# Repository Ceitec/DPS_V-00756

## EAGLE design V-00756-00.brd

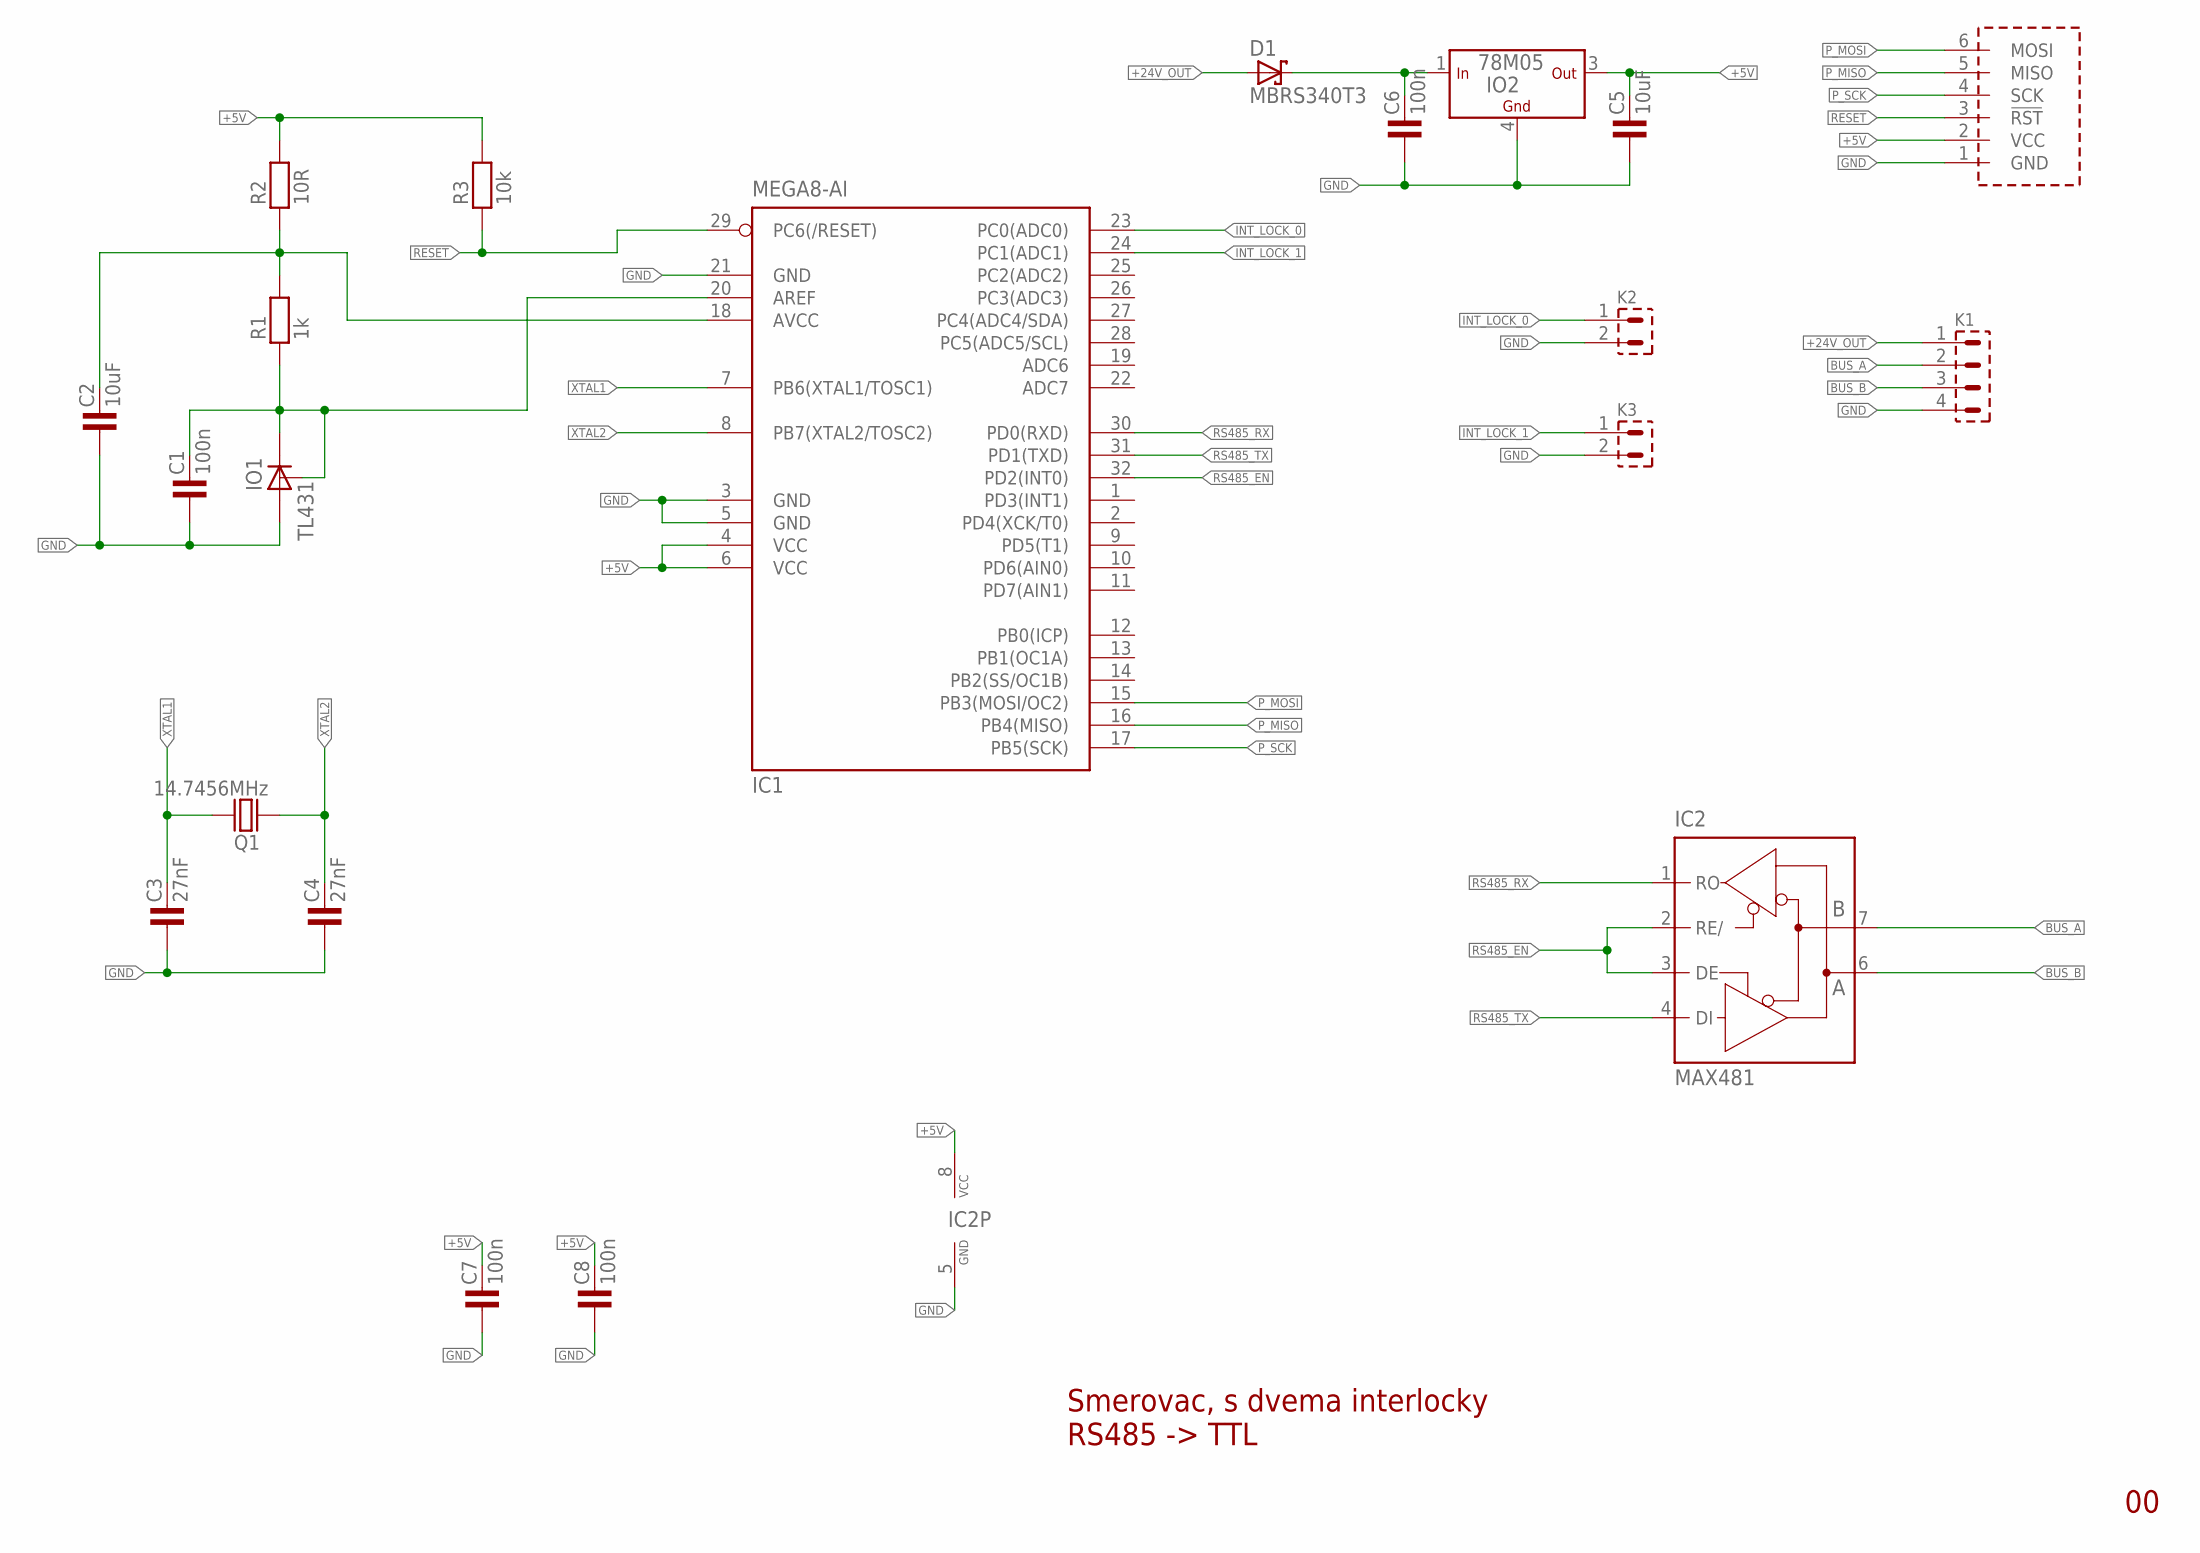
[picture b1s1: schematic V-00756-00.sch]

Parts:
C1, C6, C7, C8: 100n; 1206
C2, C5: 10uF; 1206
C3, C4: 27nF; 0805
D1: MBRS340T3; SMC
IC1: MEGA8-AI; TQFP32-08
IC2: MAX481; SO08
IO1: TL431; SOT23
IO2: 78M05; DPAK
K1: PSH02-04W
K2, K3: PSH02-02W
Q1: 14.7456MHz; HC-49U
R1: 1k; 1206
R2: 10R; 1206
R3: 10k; 1206
U$1: AVR_PROG_SPI; PSH02-06P

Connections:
+5V: C5.2, C7.2, C8.2, IC1.4 (VCC), IC1.6 (VCC), IC2.8 (VCC), IO2.3 (OUT), R2.2, R3.2, U$1.2 (VCC)
+24V: C6.2, D1.C, IO2.1 (IN)
+24V_OUT: D1.A, K1.1
AREF: C1.2, IC1.20 (AREF), IO1.1 (C), IO1.2 (R), R1.1
AVCC: C2.2, IC1.18 (AVCC), R1.2, R2.1
BUS_A: IC2.7 (B), K1.2
BUS_B: IC2.6 (A), K1.3
GND: C1.1, C2.1, C3.1, C4.1, C5.1, C6.1, C7.1, C8.1, IC1.3 (GND), IC1.5 (GND), IC1.21 (GND), IC2.5 (GND), IO1.3 (A), IO2.4 (GND), K1.4, K2.2, K3.2, U$1.1 (GND)
INT_LOCK_0: IC1.23 (PC0(ADC0)), K2.1
INT_LOCK_1: IC1.24 (PC1(ADC1)), K3.1
P_MISO: IC1.16 (PB4(MISO)), U$1.5 (MISO)
P_MOSI: IC1.15 (PB3(MOSI/OC2)), U$1.6 (MOSI)
P_SCK: IC1.17 (PB5(SCK)), U$1.4 (SCK)
RESET: IC1.29 (PC6(/RESET)), R3.1, U$1.3 (!RST)
RS485_EN: IC1.32 (PD2(INT0)), IC2.2 (RE/), IC2.3 (DE)
RS485_RX: IC1.30 (PD0(RXD)), IC2.1 (RO)
RS485_TX: IC1.31 (PD1(TXD)), IC2.4 (DI)
XTAL1: C3.2, IC1.7 (PB6(XTAL1/TOSC1)), Q1.2
XTAL2: C4.2, IC1.8 (PB7(XTAL2/TOSC2)), Q1.1

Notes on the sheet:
Smerovac, s dvema interlocky RS485 -> TTL

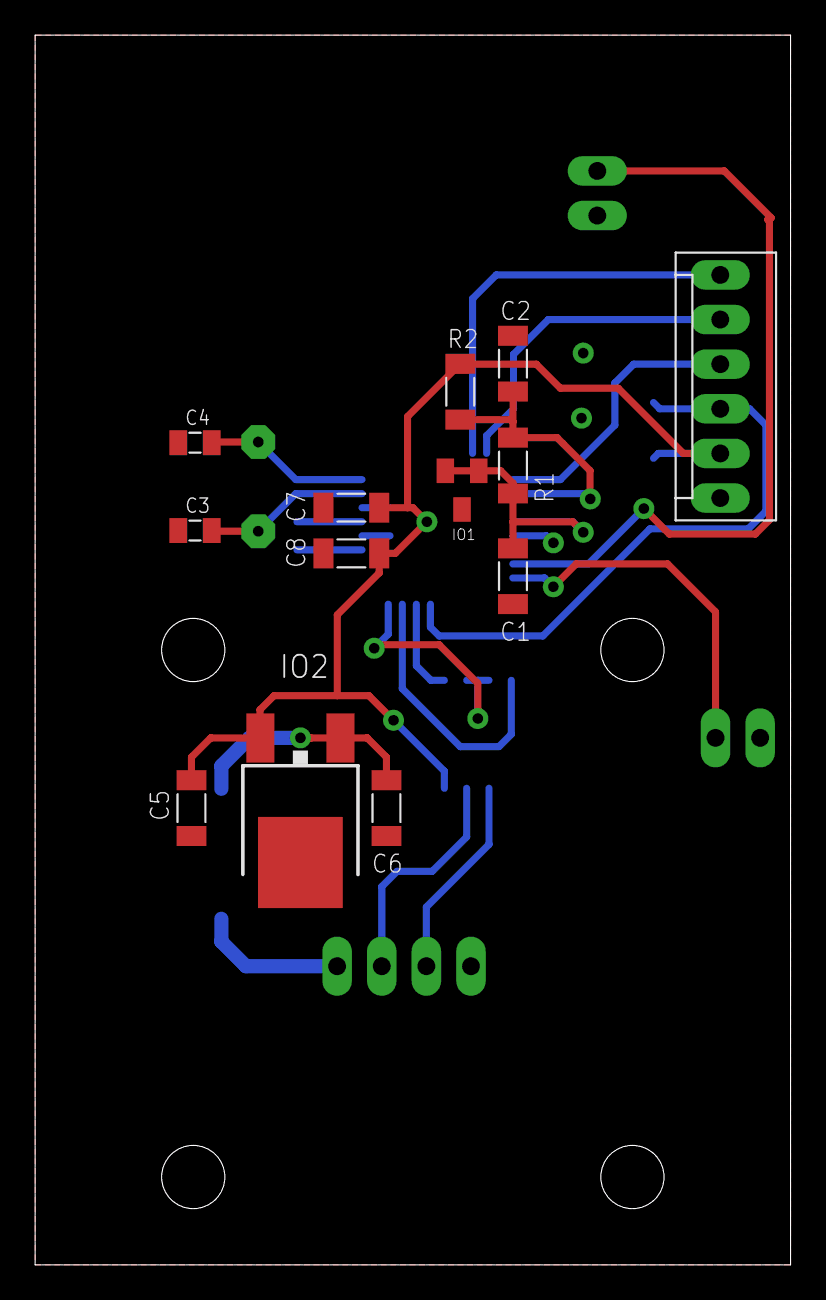
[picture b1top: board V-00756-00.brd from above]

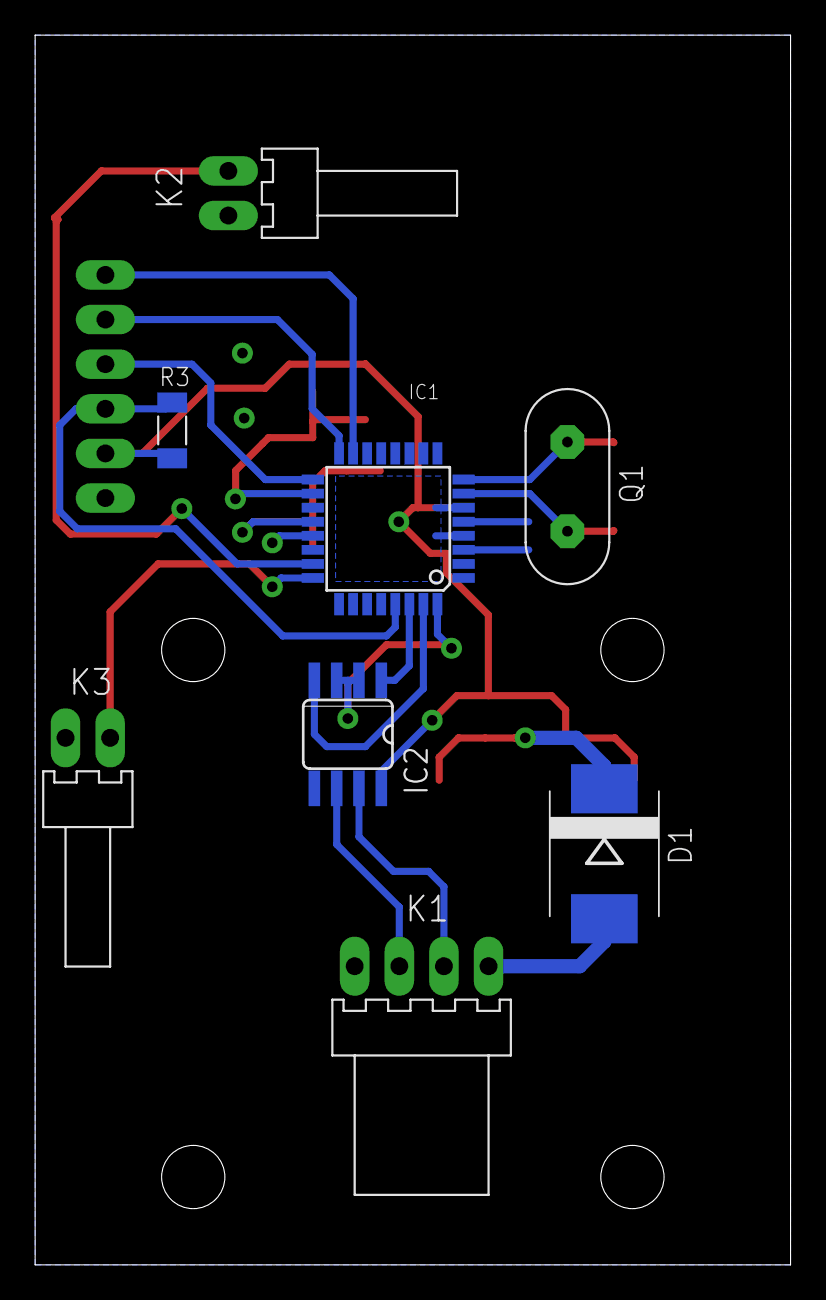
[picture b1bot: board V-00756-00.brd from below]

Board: 2 copper layers, 43.0 x 70.0 mm, 22 parts (8 on the bottom side), 19 nets.

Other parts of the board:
U$2: A4L-LOC

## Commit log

2015-12-11 :space_invader: Added .gitattributes & .gitignore files
2015-12-11 v1.1.0.1
2015-12-29 v1.1.0.2
2016-02-10 v.2.0

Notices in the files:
parts and their libraries:
Copyright (C) PaJa 2001-2014
Copyright (C) PaJa 2011-2014
